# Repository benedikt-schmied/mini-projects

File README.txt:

/brief:

 A small spotlight, small enough to be mounted on space constraint places, comprising
 RGB leds and a power microcontroller, in order to control it via networking 
 technologies (Bluetooth LE).

/nomenclature:

pro_event_light_a_mkI
 |      |       | |
 |      |       | |-- mkI  : mark one
 |      |       |---- a    : model A  
 |      |----- event_light : event light (project naming)
 |-------------------- pro : project identifier

/structure:
 |-- _application_notes:
 |-- _datasheets:
 |-- _documentation:
 |-- library
 |-- pro_event_light_a_mkI

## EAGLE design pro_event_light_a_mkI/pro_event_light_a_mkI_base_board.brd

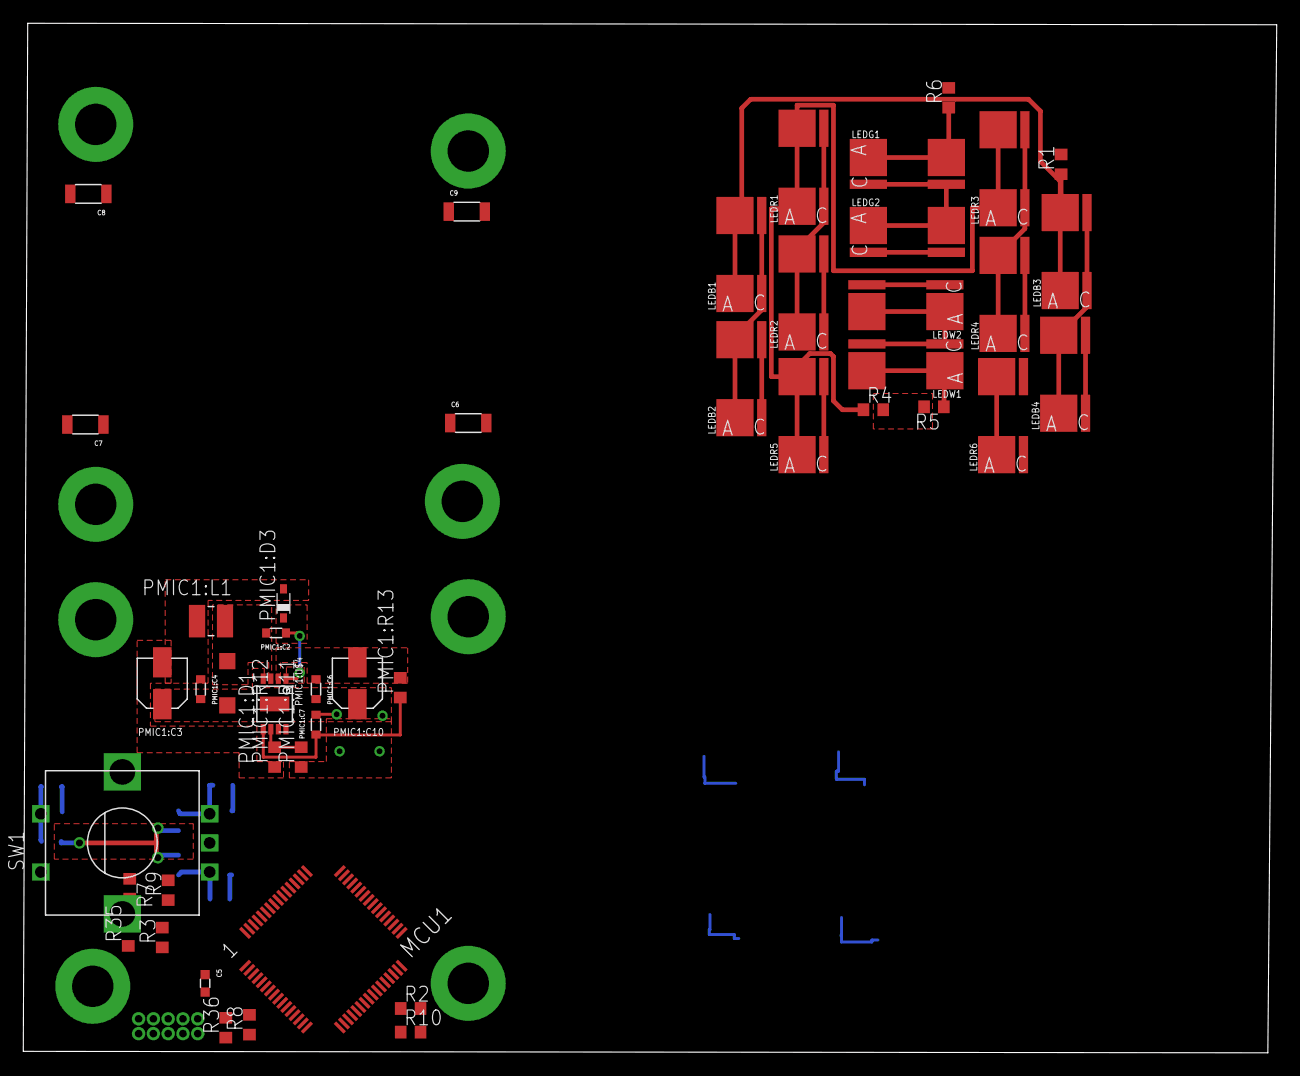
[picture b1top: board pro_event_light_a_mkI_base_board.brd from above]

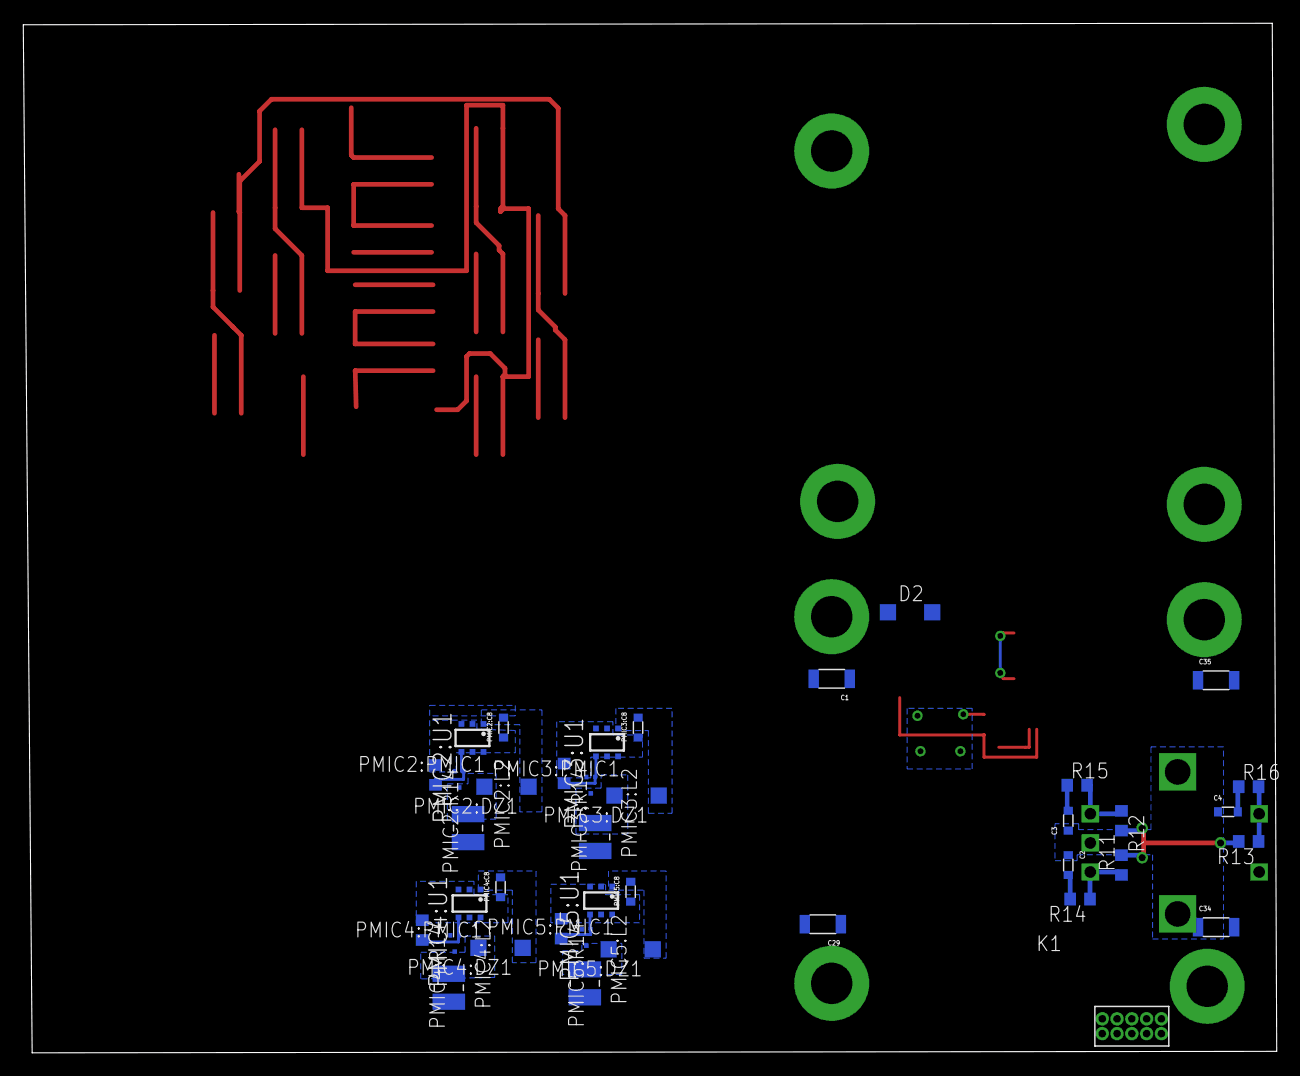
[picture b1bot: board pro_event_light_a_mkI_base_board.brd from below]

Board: 2 copper layers, 107.7 x 88.4 mm, 93 parts (39 on the bottom side), 58 nets.

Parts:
C1, C6, C7, C8, C9, C29, C34, C35: 1uF; WCAP-CSGP_1206
C2, C3, C4: 4.7pF; WCAP-CSGP_0603_WAVE
C5: 100nF; WCAP-CSGP_0603_REFLOW
D2: MBR0540T1; SOD123
K1: 62201021121
LEDB1, LEDB2, LEDB3, LEDB4: LDG5AP; P-LCC-2
LEDG1, LEDG2: LTG5AP; P-LCC-2
LEDR1, LEDR2, LEDR3, LEDR4, LEDR5, LEDR6: LRG5AP; P-LCC-2
LEDW1, LEDW2: LCWG5GP; P-LCC-2
MCU1: STM32L452RET6; LQFP64
PMIC1:C2: 220pF; WCAP-CSGP_0603_WAVE
PMIC1:C3: 45uF; 2.6X1.6X1(BXCXA)
PMIC1:C4, PMIC1:C6, PMIC1:C7: 4.7uF; WCAP-CSGP_0603_WAVE
PMIC1:C10: 10uF; 2.6X1.6X1(BXCXA)
PMIC1:D1, PMIC2:DZ1, PMIC3:DZ1, PMIC4:DZ1, PMIC5:DZ1: MBR0540T1; SOD123
PMIC1:D3: 1N4148WS; SOD323
PMIC1:L1: 1uH; WE-LQ_M
PMIC1:R11: 10K; R0603
PMIC1:R12: 17K5; R0603
PMIC1:R13: 27K; R0603
PMIC1:U$4: LT1936; MSOP8
PMIC2:C8, PMIC3:C8, PMIC4:C8, PMIC5:C8: WCAP-CSGP_0603_WAVE
PMIC2:L2, PMIC3:L2, PMIC4:L2, PMIC5:L2: 68uH; WE-LQ_M
PMIC2:PMIC1, PMIC3:PMIC1, PMIC4:PMIC1, PMIC5:PMIC1: ILD4001; SC74_INFINEON
PMIC2:R14, PMIC3:R14, PMIC4:R14, PMIC5:R14: R0603
PMIC2:U1, PMIC3:U1, PMIC4:U1, PMIC5:U1: PMXB56EN; DFN1010D-3
R1, R2, R4, R5, R6: R0603
R3, R7, R8, R9, R10: 0R0; R0603
R11, R12, R13: 22K; R0603
R14, R15, R16: 100; R0603
R35, R36: 0R; R0603
SW1: ALPS_EC11D
U$1, U$2, U$3, U$4, U$8, U$10, U$11, U$15: PCB_MOUNTING_HOLES_M3

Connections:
DRIVER_LEDB: LEDB2.3, LEDB2.4, LEDB4.3, LEDB4.4, PMIC3:L2.1
DRIVER_LEDG: LEDG2.3, LEDG2.4, PMIC2:L2.1
DRIVER_LEDR: LEDR2.3, LEDR2.4, LEDR4.3, LEDR4.4, LEDR6.3, LEDR6.4, PMIC4:L2.1
DRIVER_LEDW: LEDW2.3, LEDW2.4, PMIC5:L2.1
ENCODER_A: C2.2, MCU1.26, R14.2
ENCODER_B: C3.2, MCU1.27, R15.1
ENCODER_D: C4.2, MCU1.28, R16.1
GND_MCU: C1.2, C2.1, C3.1, C4.1, C5.1, C6.2, C7.2, C8.2, C9.2, C29.2, C34.2, C35.2, K1.2, K1.3, MCU1.18, MCU1.47, MCU1.63, PMIC1:C3.1, PMIC1:C4.2, PMIC1:C6.2, PMIC1:C7.2, PMIC1:C10.1, PMIC1:D1.A, PMIC1:R11.1, PMIC1:U$4.4, PMIC1:U$4.9, PMIC2:C8.1, PMIC2:PMIC1.2, PMIC2:PMIC1.5, PMIC2:R14.1, PMIC2:U1.2, PMIC3:C8.1, PMIC3:PMIC1.2, PMIC3:PMIC1.5, PMIC3:R14.1, PMIC3:U1.2, PMIC4:C8.1, PMIC4:PMIC1.2, PMIC4:PMIC1.5, PMIC4:R14.1, PMIC4:U1.2, PMIC5:C8.1, PMIC5:PMIC1.2, PMIC5:PMIC1.5, PMIC5:R14.1, PMIC5:U1.2, R7.2, R8.2, R9.2, R10.2, R35.2, R36.2, SW1.C, SW1.D, SW1.GND1, SW1.GND2
LEDB: MCU1.15, PMIC3:PMIC1.3
LEDG: MCU1.14, PMIC2:PMIC1.3
LEDR: MCU1.16, PMIC4:PMIC1.3
LEDW: MCU1.17, PMIC5:PMIC1.3
unnamed: R11.1, R14.1, SW1.A
unnamed: R12.1, R15.2, SW1.B
unnamed: LEDG1.3, LEDG1.4, LEDG2.1, LEDG2.2
unnamed: LEDB1.3, LEDB1.4, LEDB2.1, LEDB2.2
unnamed: C6.1, U$2.PIN1
unnamed: LEDB3.3, LEDB3.4, LEDB4.1, LEDB4.2
unnamed: LEDR1.3, LEDR1.4, LEDR2.1, LEDR2.2
unnamed: C7.1, U$1.PIN1
unnamed: C29.1, U$11.PIN1
unnamed: C8.1, U$3.PIN1
unnamed: C9.1, U$4.PIN1
unnamed: LEDR3.3, LEDR3.4, LEDR4.1, LEDR4.2
unnamed: LEDR5.3, LEDR5.4, LEDR6.1, LEDR6.2
unnamed: C34.1, U$10.PIN1
unnamed: R13.1, R16.2, SW1.E
unnamed: C35.1, U$15.PIN1
unnamed: C1.1, U$8.PIN1
unnamed: C5.2, MCU1.1, R3.1
unnamed: MCU1.3, R10.1
unnamed: LEDW1.3, LEDW1.4, LEDW2.1, LEDW2.2
unnamed: MCU1.5, R9.1
unnamed: MCU1.6, R7.1
PMIC1:N$28: PMIC1:U$4.7, PMIC1:U$4.8
PMIC1:N$30: PMIC1:C7.1, PMIC1:R13.1, PMIC1:U$4.5
PMIC1:N$35: PMIC1:R11.2, PMIC1:R12.2, PMIC1:U$4.6
PMIC1:PMIC_LT1936_BOOST: PMIC1:C2.1, PMIC1:D3.C, PMIC1:U$4.1
PMIC1:PMIC_LT1936_SW: PMIC1:C2.2, PMIC1:D1.C, PMIC1:L1.1, PMIC1:U$4.3
PMIC2:N$2: PMIC2:PMIC1.4, PMIC2:R14.2, PMIC2:U1.1
PMIC2:N$29: PMIC2:DZ1.A, PMIC2:L2.2, PMIC2:U1.3
PMIC3:N$2: PMIC3:PMIC1.4, PMIC3:R14.2, PMIC3:U1.1
PMIC3:N$29: PMIC3:DZ1.A, PMIC3:L2.2, PMIC3:U1.3
PMIC4:N$2: PMIC4:PMIC1.4, PMIC4:R14.2, PMIC4:U1.1
PMIC4:N$29: PMIC4:DZ1.A, PMIC4:L2.2, PMIC4:U1.3
PMIC5:N$2: PMIC5:PMIC1.4, PMIC5:R14.2, PMIC5:U1.1
PMIC5:N$29: PMIC5:DZ1.A, PMIC5:L2.2, PMIC5:U1.3
S3V3_MCU_VDD: MCU1.19, MCU1.32, MCU1.64, PMIC1:C3.2, PMIC1:C4.1, PMIC1:D3.A, PMIC1:L1.2, PMIC1:R12.1, R2.1, R3.2, R11.2, R12.2, R13.2
SUPPLY_24V: D2.C, PMIC1:C6.1, PMIC1:C10.2, PMIC1:R13.2, PMIC1:U$4.2, PMIC2:C8.2, PMIC2:DZ1.C, PMIC2:PMIC1.1, PMIC3:C8.2, PMIC3:DZ1.C, PMIC3:PMIC1.1, PMIC4:C8.2, PMIC4:DZ1.C, PMIC4:PMIC1.1, PMIC5:C8.2, PMIC5:DZ1.C, PMIC5:PMIC1.1, R1.2, R4.2, R5.2, R6.2
SWCLK: K1.9, MCU1.49
SWDIO: K1.10, MCU1.46
SWO: K1.8, R35.1
TDI: K1.7, R36.1
VSENSE_LEDB: LEDB1.1, LEDB1.2, LEDB3.1, LEDB3.2, PMIC3:PMIC1.6, R1.1
VSENSE_LEDG: LEDG1.1, LEDG1.2, PMIC2:PMIC1.6, R6.1
VSENSE_LEDR: LEDR1.1, LEDR1.2, LEDR3.1, LEDR3.2, LEDR5.1, LEDR5.2, PMIC4:PMIC1.6, R4.1
VSENSE_LEDW: LEDW1.1, LEDW1.2, PMIC5:PMIC1.6, R5.1
VTREF: K1.1, R2.2

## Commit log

2017-06-13 initial check in of README.txt in order to test handling of git - hub
2017-06-15 first implementation of LT1936
2017-06-19 now having the STM32L452 aboard as well as the LED controller from Infineon
2017-06-21 included rotary switch (also in separate library)
2017-06-23 some comments and periphery on LT1936
2017-06-26 commit prior of trying to clone some parts
2017-06-26 first attempt using modules
2017-06-27 first layout of 4001
2017-07-23 preliminary layout for LT1936
2017-07-23 first layout for IL4001
2017-07-23 modelled all four IL4001 PMICs
2017-07-23 layout for all 4 IL4001
2017-07-23 first layout for LEDs
2017-07-23 cannot accomplished one board, hence split up into two boards
2017-07-23 first push to remote repository
2017-07-24 first draft of README.txt
2017-07-24 saving an intermediate 'snapshot' -> maybe we have to revert afterwards. This layout will take all Infineon chips on the 'power' board
2017-07-24 final commit for today. LEDs are rearranged, looks pretty good right now
2017-07-26 deleted unnecessary bak up files
2017-07-26 exluded temporary / bakup files from eagle
2017-07-26 exluded temporary / bakup files from eagle changed mail address
2017-11-15 deleted all libraries, will be replaced by submodules
2017-11-15 included some submodules that have previously been located in this project itself submodules are: mod_eagle_library_... .. MCU_CPU .. PMIC .. discrete_elements .. switches
2017-11-15 corrected some traces within the schematic
2017-11-15 new commits in various libraries

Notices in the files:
parts and their libraries:
Board_to_Board_Connectors_rev15d: Copyright: Würth Elektronik
